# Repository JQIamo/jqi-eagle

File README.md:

# JQI Circuit Designs

This repository (now a single README file) lists the electronics/instrumentation circuits designed and built at the JQI.

As of commit [ac6f3059ff](https://github.com/JQIamo/jqi-eagle/tree/ac6f3059ffcecc210dcfaeac3f5a702c11303dd0), individual electronics design projects are split into their own individual git repository. This is more in line with the git versioning philosophy, and will generally make life easier.

Because each project now has a separate repository, this README page should be used to host a quick one or two sentence description of each project, and a link to the corresponding repository.

## Getting started with EAGLE

First, download Eagle. There is a free version available, or ask around for
the site license. Then, configure your Eagle according to [eagle-config](https://github.com/JQIamo/eagle-config).

## Beginning a new project

If you are beginning a new circuit design, first make sure there isn't already one that meets your needs! Then, you should use the Eagle control panel to create a new project, and initialize a Git repository in the newly created directory. Add a description via the Eagle control panel (this takes HTML formatting, btw), add a new schematic file, and you're off to the races!

Once you are at a point you'd like to share, or are done with prototyping/at a stable version, create a new repository under the JQIamo organization, and push your local changes (eg, with `git remote add origin git@github.com:JQIamo/new-repo.git` then `git push origin -u master`, or with the GitHub for Mac/Windows client.)

In your project, you should try to include other auxiliary files (BOM, etc.) that might be useful for someone trying to fabricate the circuit for their lab.

## Where should general project documentation go?

For now, probably on the JQI wiki. But, ultimately I feel it makes the most sense to go in a `README` file on GitHub. Perhaps we can replicate @ZJ's awesome Dokuwiki plugin for bug tracking to pull GitHub documentation into the wiki page? However, this does present an odd workflow for people who have a wiki account but no GitHub account.

# List of Projects

## AOM Driver

[https://github.com/JQIamo/aom-driver](https://github.com/JQIamo/aom-driver)

2W AOM driver, with several fun bells and whistles. Includes an integrated VCO (with optional external RF input), power attenuation control, and integrated PI feedback control to either stabalize RF power or optical power in an intensity lock setup.

## DC/RF Adder

[https://github.com/JQIamo/dc-rf-adder](https://github.com/JQIamo/dc-rf-adder)

Simple 4-channel op-amp adder circuit, to add a DC offset to an RF signal. "DC" input has ~ 200kHz bandwidth, and "RF" input has ~ 2.5 MHz bandwidth. See project page for more details and measured transfer function.

## RF Transimpedance Amplifier

[https://github.com/JQIamo/rf-transimpedance-amplifier](https://github.com/JQIamo/rf-transimpedance-amplifier)

AC-coupled transimpedance amplifier, desigend for use in (eg) beatnote or PDH locking.

## Rotary Encoder Breakout

[https://github.com/JQIamo/rotary-encoder-breakout](https://github.com/JQIamo/rotary-encoder-breakout)

Breakout boards for use with the Bounrs PEC09-series rotary encoder. Includes a breakout adapter to interface with an Arduino, and supports daisy-chaning several encoders on the same signal line using CAT5 cable. Useful for placing DAC control knobs around the lab.

## Low noise 5A linear power supply for Eurocard boxes

[https://github.com/JQIamo/Low-noise-5A-power-supply](https://github.com/JQIamo/Low-noise-5A-power-supply)

This +- 15 V power supply has a ripple of 400uV at full load. It has a form factor that makes it easy to be mounted on the back panel of a 4U 19'' box. It is intended as a replacement for Power-One modules.

## Compact high voltage driver for piezo actuators

This compact piezo high voltage driver has its own internal low power high voltage source, is compatibile with Eurocard backplane and has a limited (24 Vpp) range of modulation around an arbitrary set point. 
Designed by Swarnav Banik, Neal Pisenti and Alessandro Restelli Joint Quantum Institute.

[https://github.com/JQIamo/piezo-compact-high-voltage-driver](https://github.com/JQIamo/piezo-compact-high-voltage-driver)

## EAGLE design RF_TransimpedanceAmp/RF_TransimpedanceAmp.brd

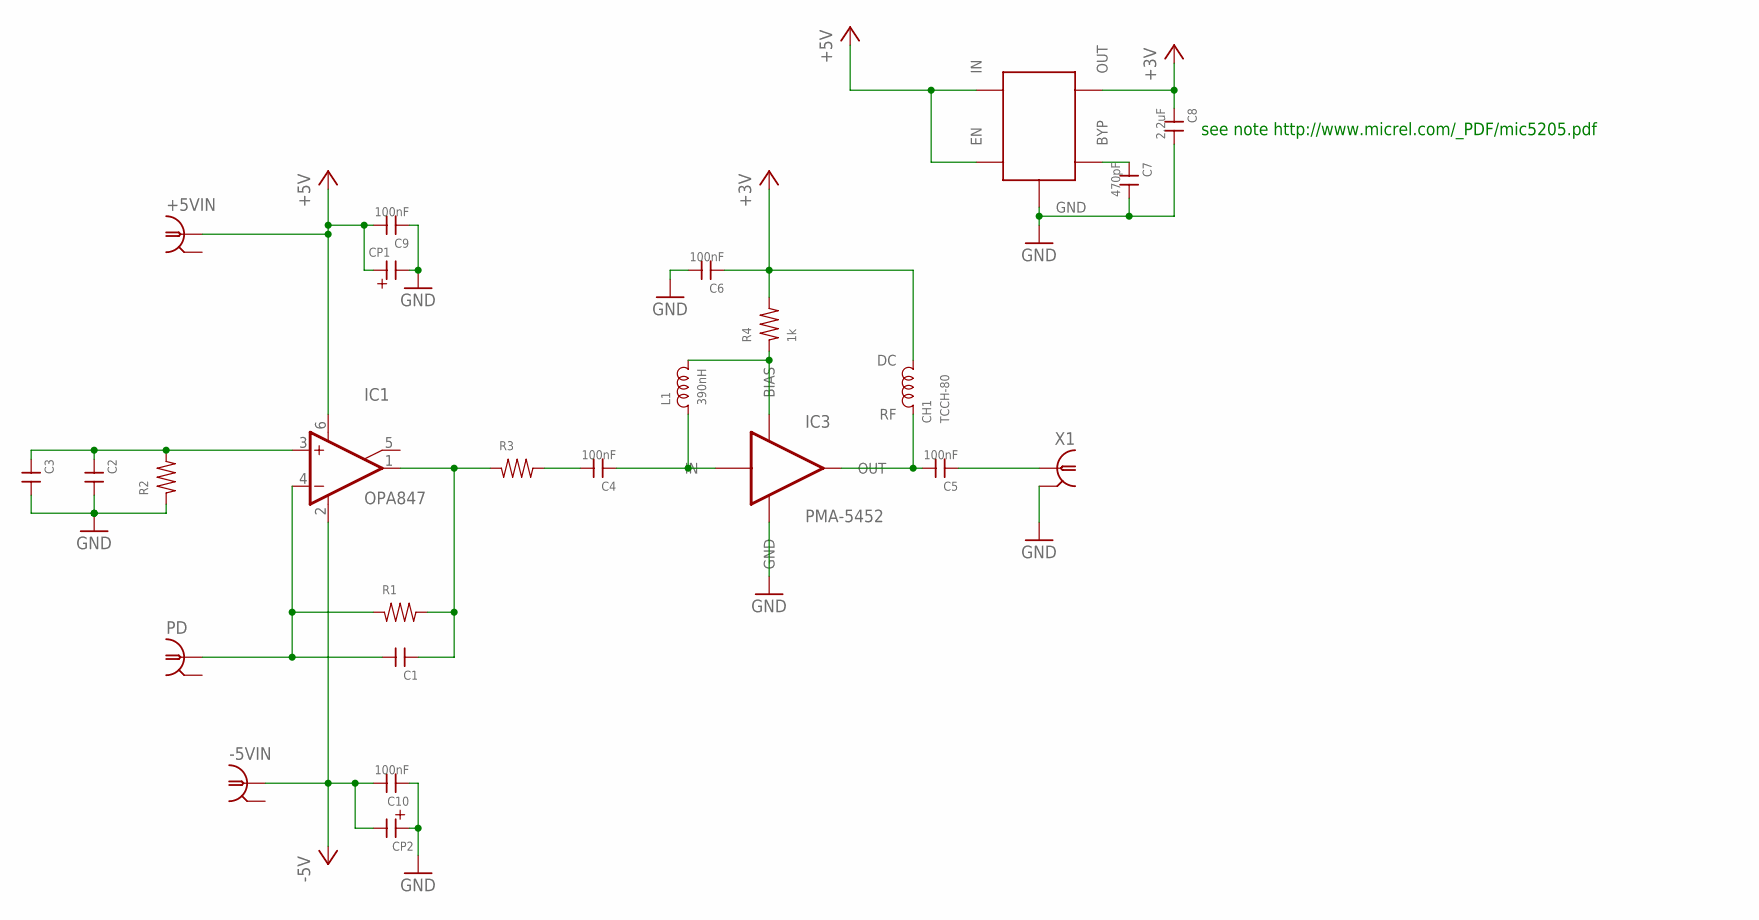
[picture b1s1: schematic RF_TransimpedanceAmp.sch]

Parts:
+5VIN: UMC
-5VIN: UMC
C1, C2, C3: CAP0201; 0201
C4, C5, C6, C9, C10: 100nF; 0201
C7: 470pF; 0201
C8: 2.2uF; 0402
CH1: TCCH-80; GU1604
CP1, CP2: CAP-POL0603; 0603P
IC1: OPA847; SOT23-6
IC3: PMA-5452; DQ849
L1: 390nH; 0402
PD: SMA; SMA-SMT; DIGIKEY J819-ND
R1, R2, R3: RES0201; 0201
R4: 1k; 0402
U$1: MIC5205; SOT23-5L
X1: UMC

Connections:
+3V: C6.P$1, C8.1, CH1.P$3 (DC), R4.2, U$1.5 (OUT)
+5V: +5VIN.P$1 (1), C9.P$2, CP1.1, IC1.6 (V+), U$1.1 (IN), U$1.3 (EN)
-5V: -5VIN.P$1 (1), C10.P$2, CP2.2, IC1.2 (V-)
GND: C2.P$2, C3.P$2, C6.P$2, C7.P$2, C8.2, C9.P$1, C10.P$1, CP1.2, CP2.1, IC3.P$GND (GND), R2.P$1, U$1.2 (GND), X1.P$2 (2), X1.P$3 (2)
unnamed: C2.P$1, C3.P$1, IC1.3 (+IN), R2.P$2
unnamed: C1.P$2, IC1.4 (-IN), PD.P$1 (1), R1.P$1
unnamed: C1.P$1, IC1.1 (OUT), R1.P$2, R3.P$1
unnamed: C4.P$2, R3.P$2
unnamed: C4.P$1, IC3.P$1 (IN), L1.1
unnamed: C5.P$2, CH1.P$1 (RF), IC3.P$6 (OUT)
unnamed: C5.P$1, X1.P$1 (1)
unnamed: IC3.P$7 (BIAS), L1.2, R4.1
unnamed: C7.P$1, U$1.4 (BYP)

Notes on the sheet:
see note http://www.micrel.com/_PDF/mic5205.pdf

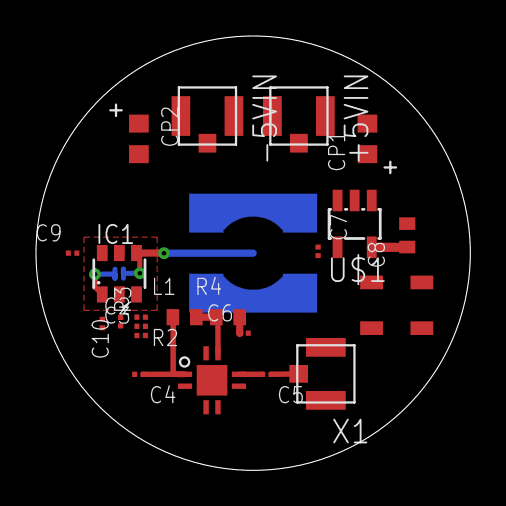
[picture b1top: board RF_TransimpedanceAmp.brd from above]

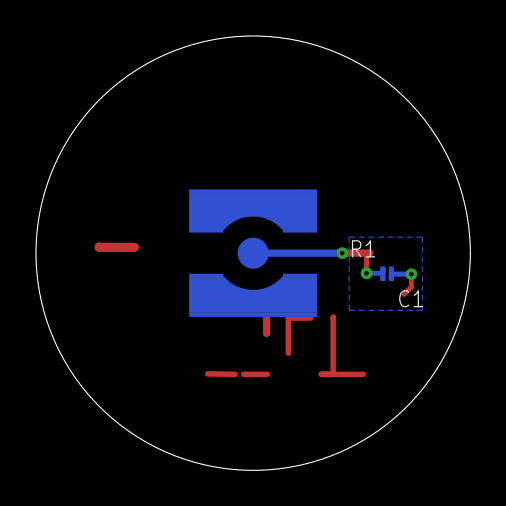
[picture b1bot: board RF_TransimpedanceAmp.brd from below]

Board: 2 copper layers, 24.1 x 24.1 mm, 25 parts (3 on the bottom side), 13 nets.

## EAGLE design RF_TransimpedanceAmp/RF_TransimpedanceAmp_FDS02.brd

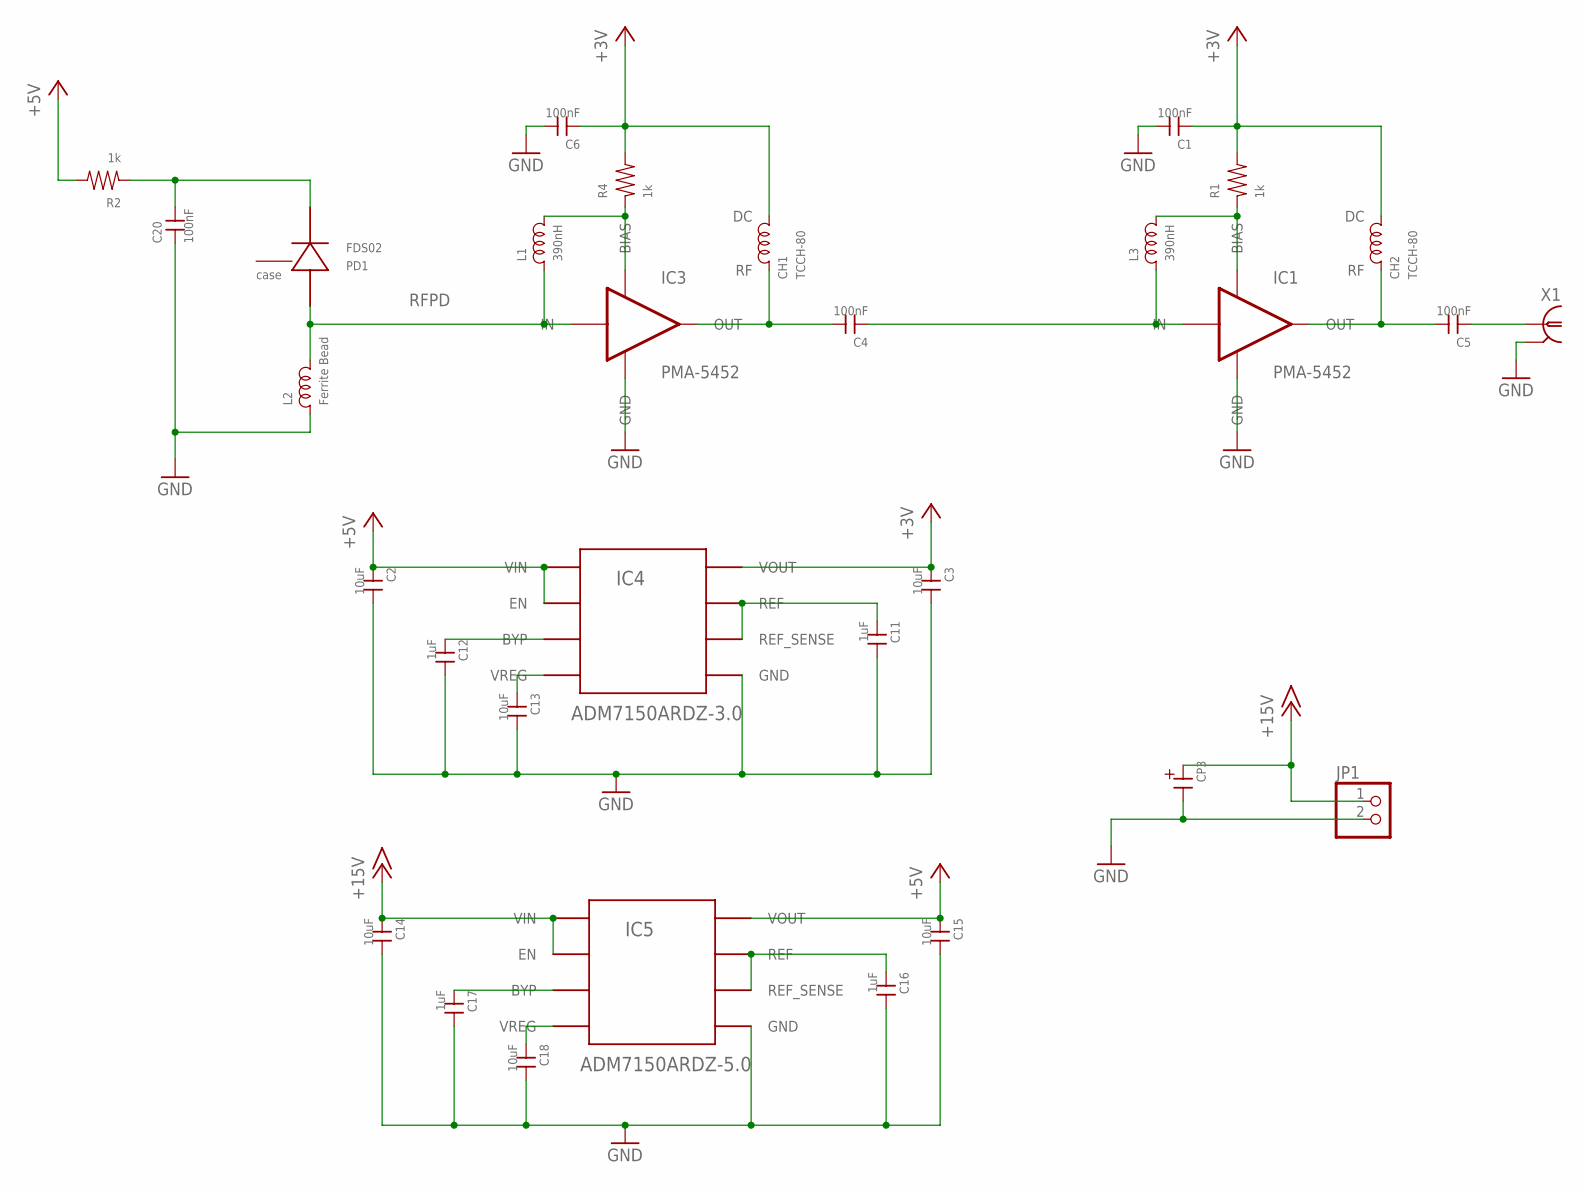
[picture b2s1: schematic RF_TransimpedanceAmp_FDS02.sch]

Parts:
C1, C4, C5, C6, C20: 100nF; 0402
C2, C3, C13, C14, C15, C18: 10uF; 1210
C11, C12, C16, C17: 1uF; 0402
CH1, CH2: TCCH-80; GU1604
CP3: CAP-POLPANASONIC_F; PANASONIC_F
IC1, IC3: PMA-5452; DQ849
IC4: ADM7150ARDZ-3.0; SO08
IC5: ADM7150ARDZ-5.0; SO08
JP1: PINHD-1X2; 1X02
L1, L3: 390nH; 0402
L2: Ferrite Bead; 1206; PARTNO 445-5223-1-ND
PD1: FDS02
R1, R2, R4: 1k; 0402
X1: SMAJ502; SMA-EDGE

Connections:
+3V: C1.1, C3.1, C6.1, CH1.P$3 (DC), CH2.P$3 (DC), IC4.2 (VOUT), R1.2, R4.2
+5V: C2.1, C15.1, IC4.7 (EN), IC4.8 (VIN), IC5.2 (VOUT), R2.2
+15V: C14.1, CP3.+, IC5.7 (EN), IC5.8 (VIN), JP1.1
GND: C1.2, C2.2, C3.2, C6.2, C11.2, C12.2, C13.2, C14.2, C15.2, C16.2, C17.2, C18.2, C20.1, CP3.-, IC1.P$GND (GND), IC3.P$GND (GND), IC4.4 (GND), IC5.4 (GND), JP1.2, L2.1, X1.G@1 (2), X1.G@2 (2), X1.G@3 (2), X1.G@4 (2)
unnamed: C11.1, IC4.5 (REF_SENSE), IC4.6 (REF)
unnamed: C5.2, CH2.P$1 (RF), IC1.P$6 (OUT)
unnamed: IC1.P$7 (BIAS), L3.2, R1.1
unnamed: C20.2, PD1.P$1 (CATHODE), R2.1
unnamed: C4.2, CH1.P$1 (RF), IC3.P$6 (OUT)
unnamed: C5.1, X1.1
unnamed: IC3.P$7 (BIAS), L1.2, R4.1
unnamed: C12.1, IC4.3 (BYP)
unnamed: C13.1, IC4.1 (VREG)
unnamed: C16.1, IC5.5 (REF_SENSE), IC5.6 (REF)
unnamed: C17.1, IC5.3 (BYP)
unnamed: C18.1, IC5.1 (VREG)
RFPD: IC3.P$1 (IN), L1.1, L2.2, PD1.P$3 (ANODE)
RFPD1: C4.1, IC1.P$1 (IN), L3.1

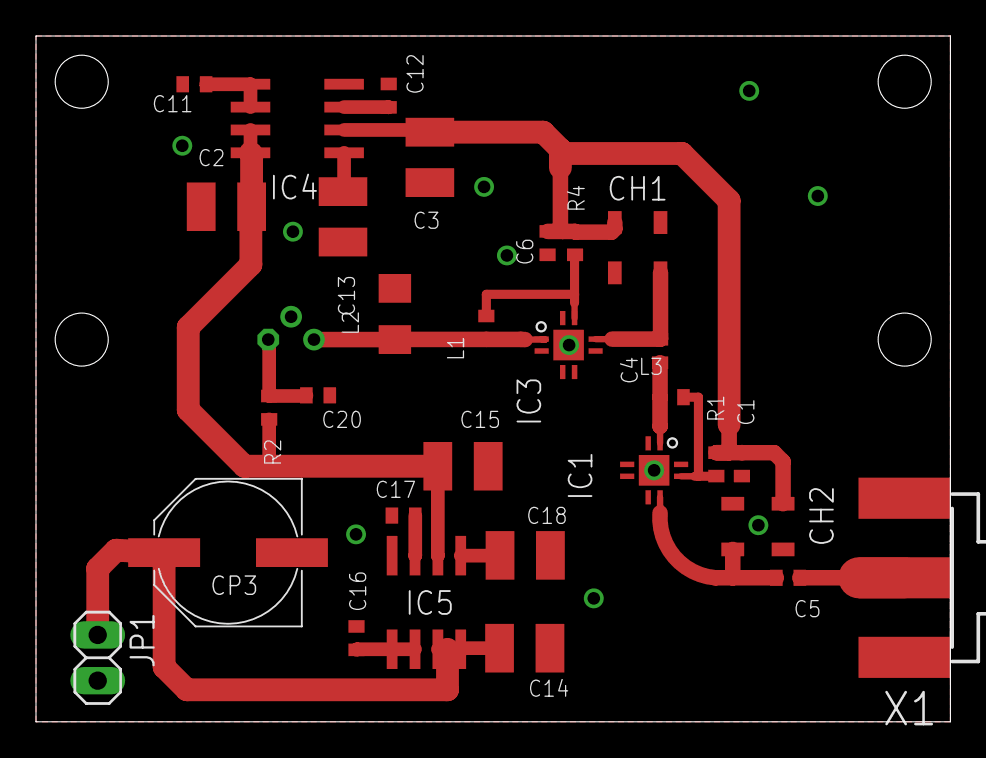
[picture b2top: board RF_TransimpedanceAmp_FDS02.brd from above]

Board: 2 copper layers, 50.8 x 38.1 mm, 31 parts (1 on the bottom side), 18 nets.

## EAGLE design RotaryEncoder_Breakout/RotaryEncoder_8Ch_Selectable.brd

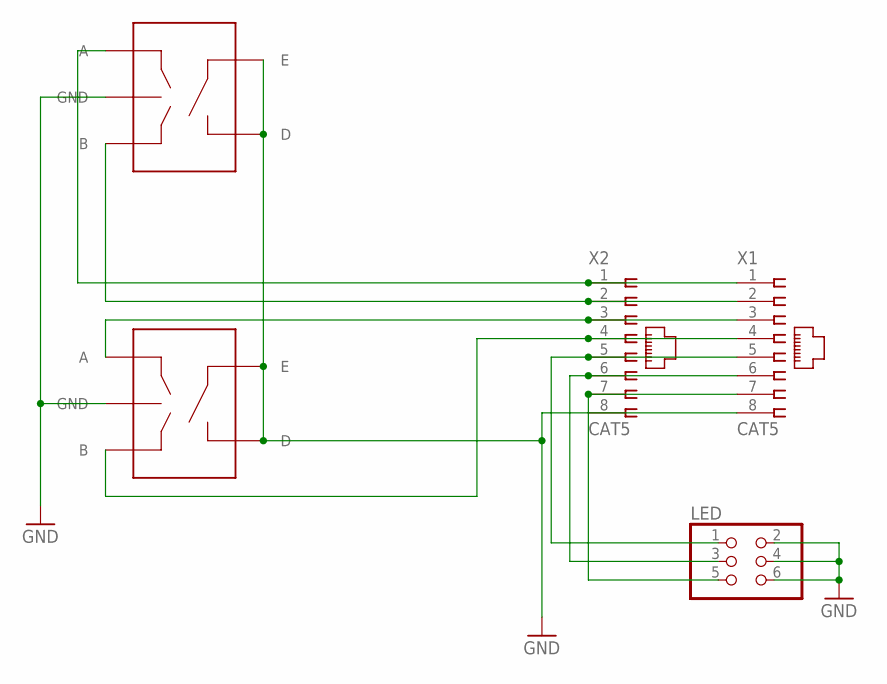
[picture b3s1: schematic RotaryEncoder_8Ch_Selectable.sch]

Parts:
ENC1, ENC2: PEC09; PEC092320FS
LED: PINHD-2X3; 2X03
X1, X2: CAT5; 555164-1

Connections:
GND: ENC1.C (GND), ENC1.D, ENC1.E, ENC2.C (GND), ENC2.D, ENC2.E, LED.2, LED.4, LED.6, X1.8, X2.8
unnamed: LED.3, X1.6, X2.6
unnamed: LED.5, X1.7, X2.7
unnamed: LED.1, X1.5, X2.5
unnamed: ENC2.B, X1.4, X2.4
unnamed: ENC2.A, X1.3, X2.3
unnamed: ENC1.B, X1.2, X2.2
unnamed: ENC1.A, X1.1, X2.1

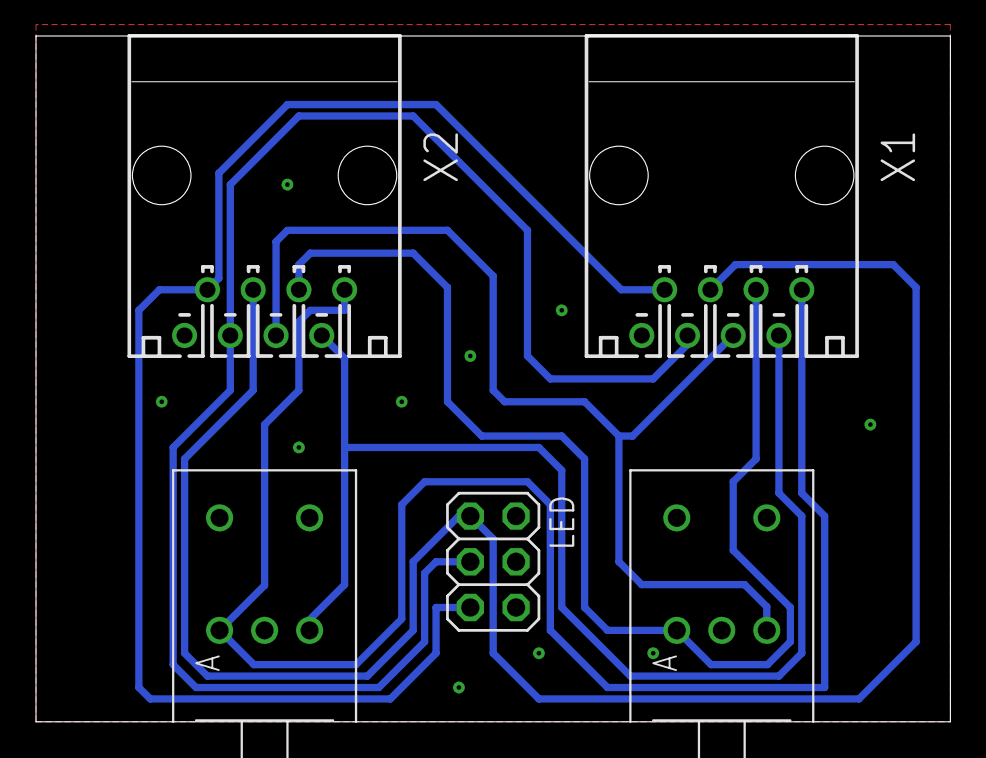
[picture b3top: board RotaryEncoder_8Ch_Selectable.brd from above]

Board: 2 copper layers, 50.8 x 38.1 mm, 5 parts (0 on the bottom side), 8 nets.

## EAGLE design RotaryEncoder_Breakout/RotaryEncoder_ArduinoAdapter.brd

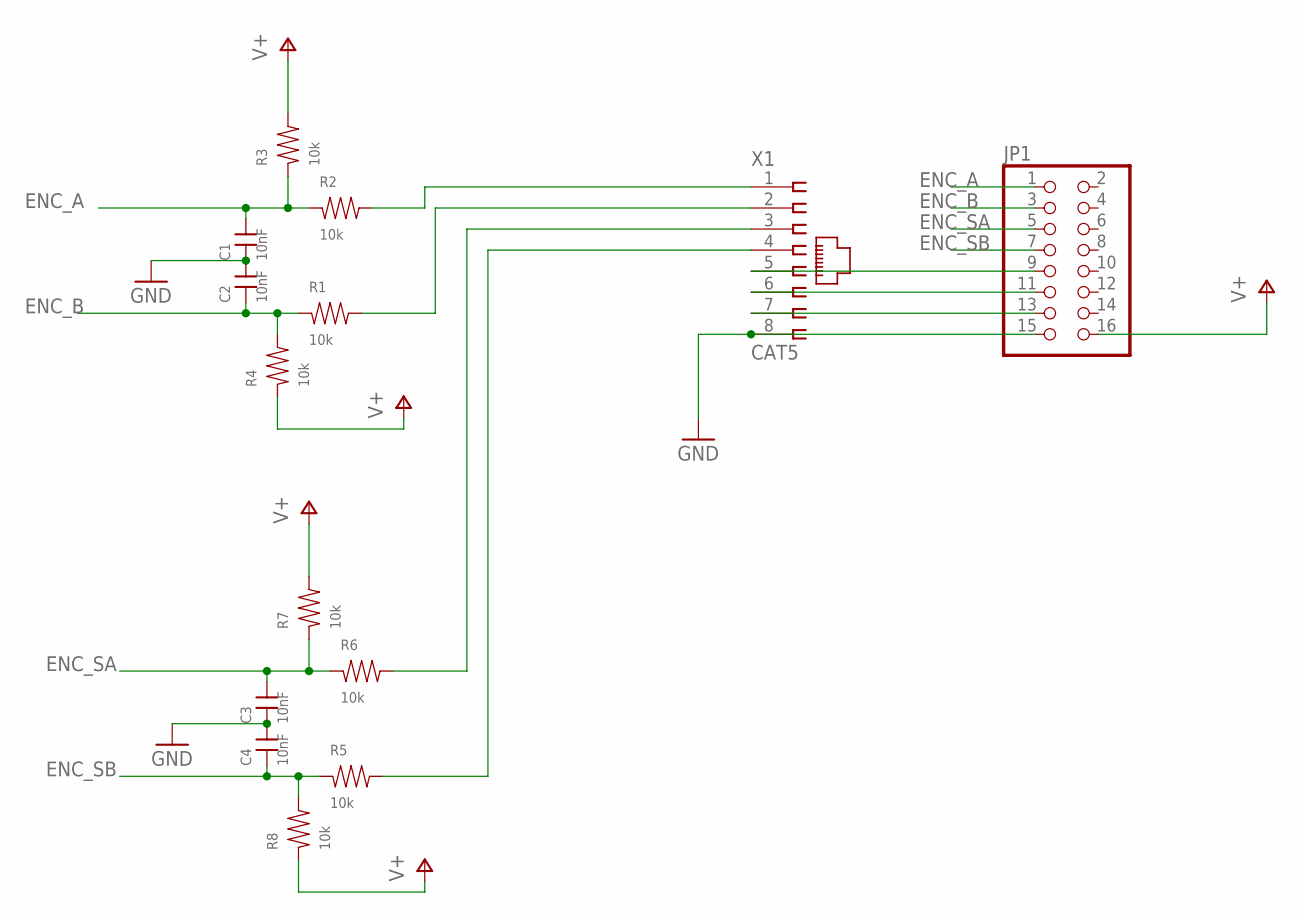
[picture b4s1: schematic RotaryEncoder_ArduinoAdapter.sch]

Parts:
C1, C2, C3, C4: 10nF; 0603
JP1: PINHD-2X8; 2X08
R1, R2, R3, R4, R5, R6, R7, R8: 10k; 0603
X1: CAT5; 555164-1

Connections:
ENC_A: C1.2, JP1.1, R2.1, R3.1
ENC_B: C2.1, JP1.3, R1.1, R4.2
ENC_SA: C3.2, JP1.5, R6.1, R7.1
ENC_SB: C4.1, JP1.7, R5.1, R8.2
GND: C1.1, C2.2, C3.1, C4.2, JP1.15, X1.8
unnamed: R5.2, X1.4
unnamed: R6.2, X1.3
unnamed: JP1.9, X1.5
unnamed: R1.2, X1.2
unnamed: R2.2, X1.1
unnamed: JP1.11, X1.6
unnamed: JP1.13, X1.7
V+: JP1.16, R3.2, R4.1, R7.2, R8.1

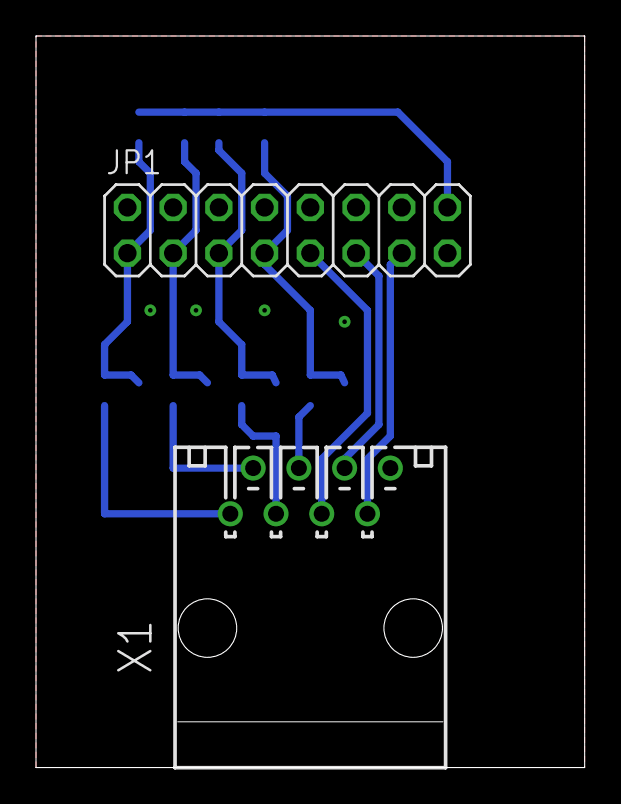
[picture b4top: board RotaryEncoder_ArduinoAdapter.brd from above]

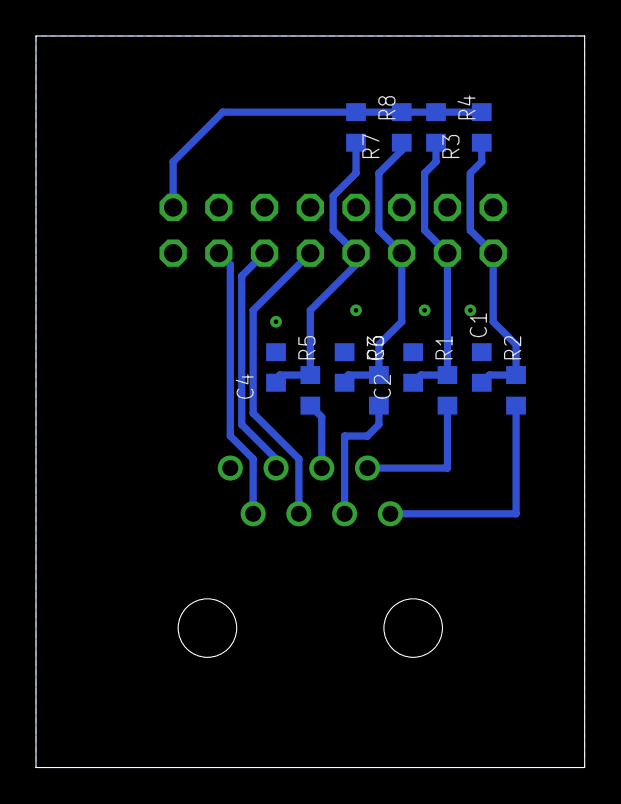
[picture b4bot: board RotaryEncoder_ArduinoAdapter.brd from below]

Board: 2 copper layers, 30.5 x 40.6 mm, 14 parts (12 on the bottom side), 13 nets.

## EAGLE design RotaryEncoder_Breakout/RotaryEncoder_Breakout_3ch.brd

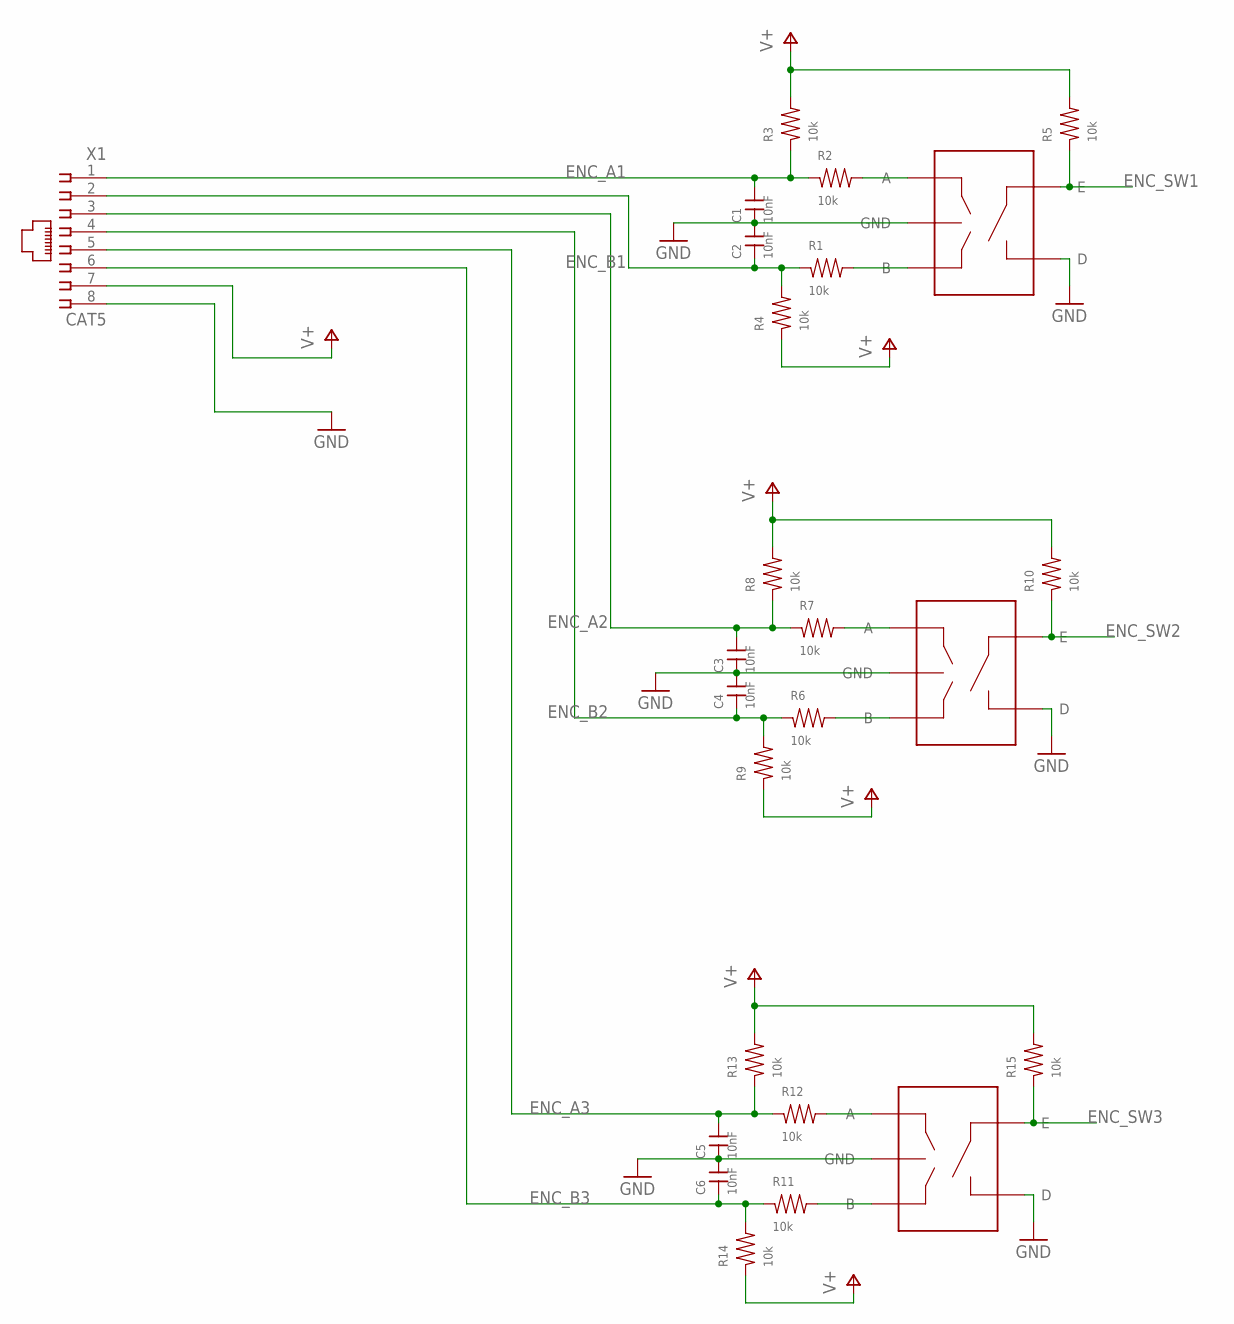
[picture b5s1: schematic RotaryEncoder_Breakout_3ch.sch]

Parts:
C1, C2, C3, C4, C5, C6: 10nF; 0603
ENC1, ENC2, ENC3: PEC09; PEC092320FS
R1, R2, R3, R4, R5, R6, R7, R8, R9, R10, R11, R12, R13, R14, R15: 10k; 0603
X1: CAT5; 555164-1

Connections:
ENC_A1: C1.2, R2.1, R3.1, X1.1
ENC_A2: C3.2, R7.1, R8.1, X1.3
ENC_A3: C5.2, R12.1, R13.1, X1.5
ENC_B1: C2.1, R1.1, R4.2, X1.2
ENC_B2: C4.1, R6.1, R9.2, X1.4
ENC_B3: C6.1, R11.1, R14.2, X1.6
ENC_SW1: ENC1.E, R5.1
ENC_SW2: ENC2.E, R10.1
ENC_SW3: ENC3.E, R15.1
GND: C1.1, C2.2, C3.1, C4.2, C5.1, C6.2, ENC1.C (GND), ENC1.D, ENC2.C (GND), ENC2.D, ENC3.C (GND), ENC3.D, X1.8
unnamed: ENC2.B, R6.2
unnamed: ENC2.A, R7.2
unnamed: ENC3.B, R11.2
unnamed: ENC1.B, R1.2
unnamed: ENC1.A, R2.2
unnamed: ENC3.A, R12.2
V+: R3.2, R4.1, R5.2, R8.2, R9.1, R10.2, R13.2, R14.1, R15.2, X1.7

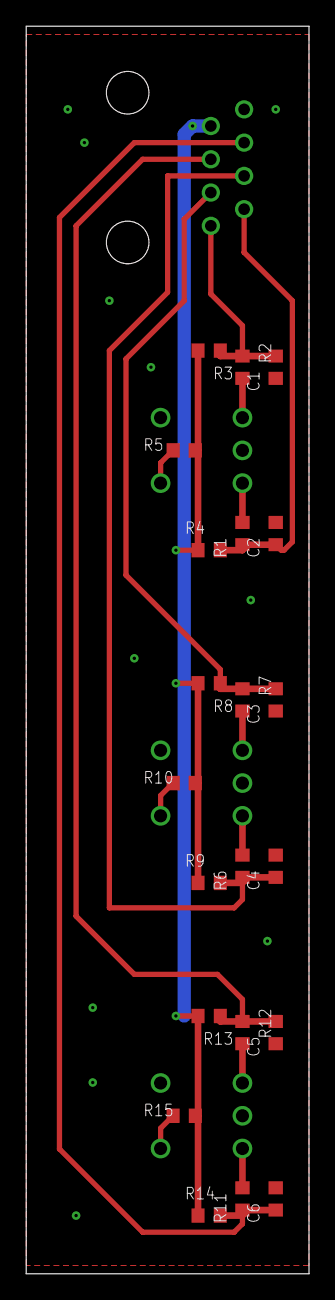
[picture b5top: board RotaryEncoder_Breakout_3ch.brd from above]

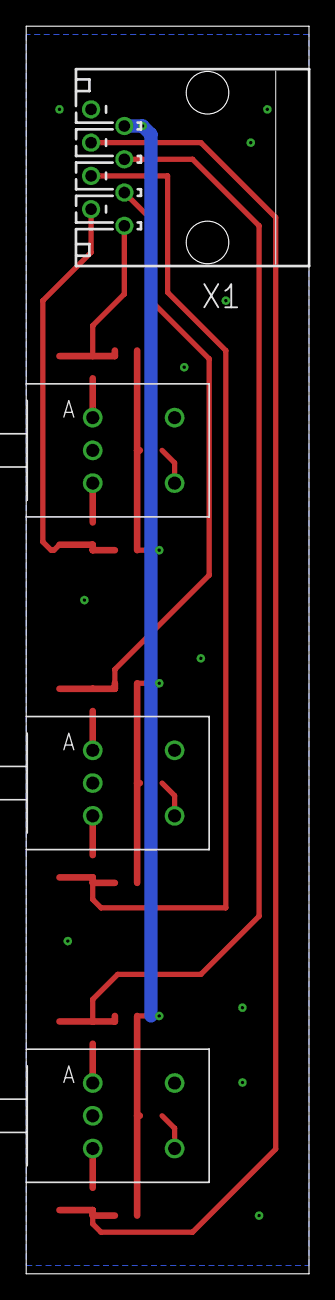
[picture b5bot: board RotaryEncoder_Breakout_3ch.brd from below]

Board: 2 copper layers, 21.6 x 95.2 mm, 25 parts (4 on the bottom side), 17 nets.

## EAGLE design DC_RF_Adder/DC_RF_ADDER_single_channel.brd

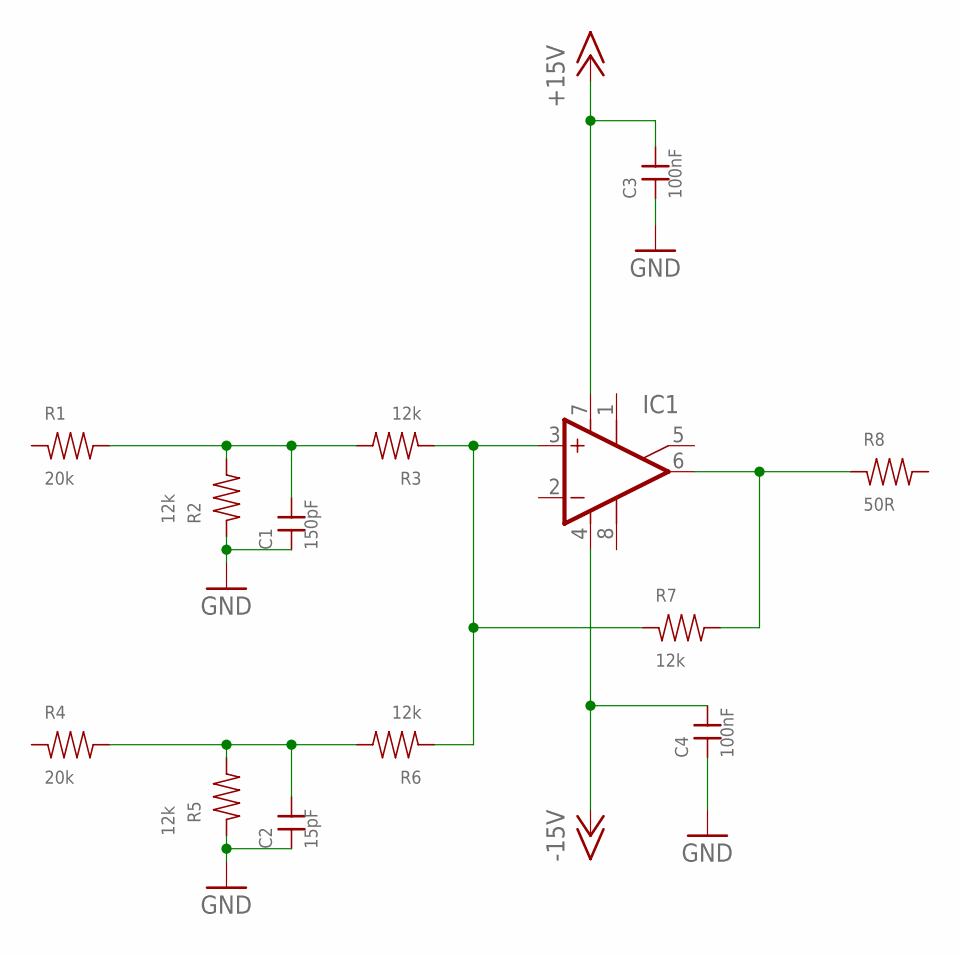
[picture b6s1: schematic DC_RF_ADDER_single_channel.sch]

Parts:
C1: 150pF; 0603
C2: 15pF; 0603
C3, C4: 100nF; 0603
IC1: OPAMP-SO; SO08
R1, R4: 20k; 0603
R2, R3, R5, R6, R7: 12k; 0603
R8: 50R; 0603

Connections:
+15V: C3.2, IC1.7 (V+)
-15V: C4.2, IC1.4 (V-)
GND: C1.1, C2.1, C3.1, C4.1, R2.1, R5.1
unnamed: C1.2, R1.2, R2.2, R3.2
unnamed: C2.2, R4.2, R5.2, R6.2
unnamed: IC1.3 (+IN), R3.1, R6.1, R7.1
unnamed: IC1.6 (OUT), R7.2, R8.1

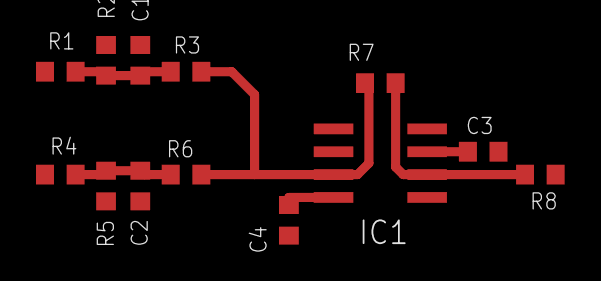
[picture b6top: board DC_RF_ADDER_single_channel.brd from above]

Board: 2 copper layers, 13 parts (0 on the bottom side), 7 nets.

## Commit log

2014-10-31 Single channel DC Adder circuit.
    Mid-development, mostly committing to initialize the repository and
    push to GitHub.
2014-10-31 Added a readme file
2014-10-31 Fixed syntax bug
2014-11-01 Initial schematic and a bit of layout for an RF transimpedance amplifier.
2014-11-01 Initial commit for rotary encoder breakout board
2014-11-01 Updated description of how schematic works/plugs together.
2014-11-03 Schematic done; routing in progress. Want to check with alessandro.
2014-11-03 3 and 4 channel rotary encoder board; still need to sort out data signals sent off-board
2014-11-11 Refactored to encoder plus secondary encoder for channel selection.
2014-11-11 Added short description for rotary encoder
2014-11-20 Initial commit for AOM driver
2014-11-21 Intermediate layout; stashing files for weekend work. Schematic still needs some work.
2014-11-21 Automatic updates to eagle .epf file
2014-11-21 Initial commit for separate schematic, for Thorlabs FDS02 fiber-connected photodiode
2014-11-24 Rough prototype of AOM board; will print and test, then optimize layout.
2014-11-25 First draft schematic and layout for FDS02 transimpedance amplifier.
    * Low transimpedance gain, followed by low-noise RF amplifier.
    * FDS02 is FC-connectorized, mount on bottom of board and standoff from front panel.
    TODO:
    * Remove -5V supply?
    * Compare OPA847 vs some FET-input op amp
    * Filtering on PD bias voltage?
2014-11-25 Minor tweaks to schematic notes; need to check 50 ohm trace width then ready to print.
2014-11-25 Adjusted center pad via in RF amp
2014-11-25 Removed OPA847, using low-noise amplifiers with 50 ohm input as transimpedance gain.
2014-11-25 Adjusted grounding vias, created gerbers
2014-11-26 V0.9 of RF_Transimpedance Amp for FDS02 diode
2014-11-26 Added pdf prints of soldermask, for use with Dynamask 5000 process.
2014-12-23 Test layout for TQP7M9106 amplifier
2014-12-23 Test board + layout for mixer as attenuator.
    Using an RF mixer as voltage-variable attenuator.
2014-12-23 Test board for AD8319 RF Log power detector and controller
2014-12-23 Added digikey part numbers, changed CLPF to 8.2pF
2014-12-31 Updated BOM parts for AOM Driver Test brd
2015-01-01 Split schematics into unique repositories.
    Deleting projects from this repository, but keeping the README file which can be updated
    with links, etc. to individual projects (ie, as a centralized list of projects/descriptions).
2015-01-01 Updated README with new details on separate repos.
    README now reflects new structure, where each project gets its own repository.
2015-01-01 Update README.md
    Fixed SHA commit link.
2015-03-24 Update README.md
    Added 5 A low noise power supply eagle project
